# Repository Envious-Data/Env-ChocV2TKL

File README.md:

# Env-ChocV2TKL
A Compact TKL layout utilizing Choc V2s and a Raspberry Pi Pico

### What this is
This is an experiment/concept, Ive been wanting a choc keyboard for a while but finding keycaps for choc V1s is rather difficult. There are also almost no ISO Keycap sets that would go on a TKL HOWEVER! it appears Choc V2s are more alike cherry LP switches which fit normal MX keycaps, they have a different footprint to Choc V1s and MX style switches (which Cherry LP is also not like normal MX).

###
feel free to steal the Choc V2 footprint out of here but, I made it by modifying the choc V1 footprint and just adjusted/resized a couple bits to fit but im not wholly sure if its correct.. well it should be as per the dimentions listed by Kailh.

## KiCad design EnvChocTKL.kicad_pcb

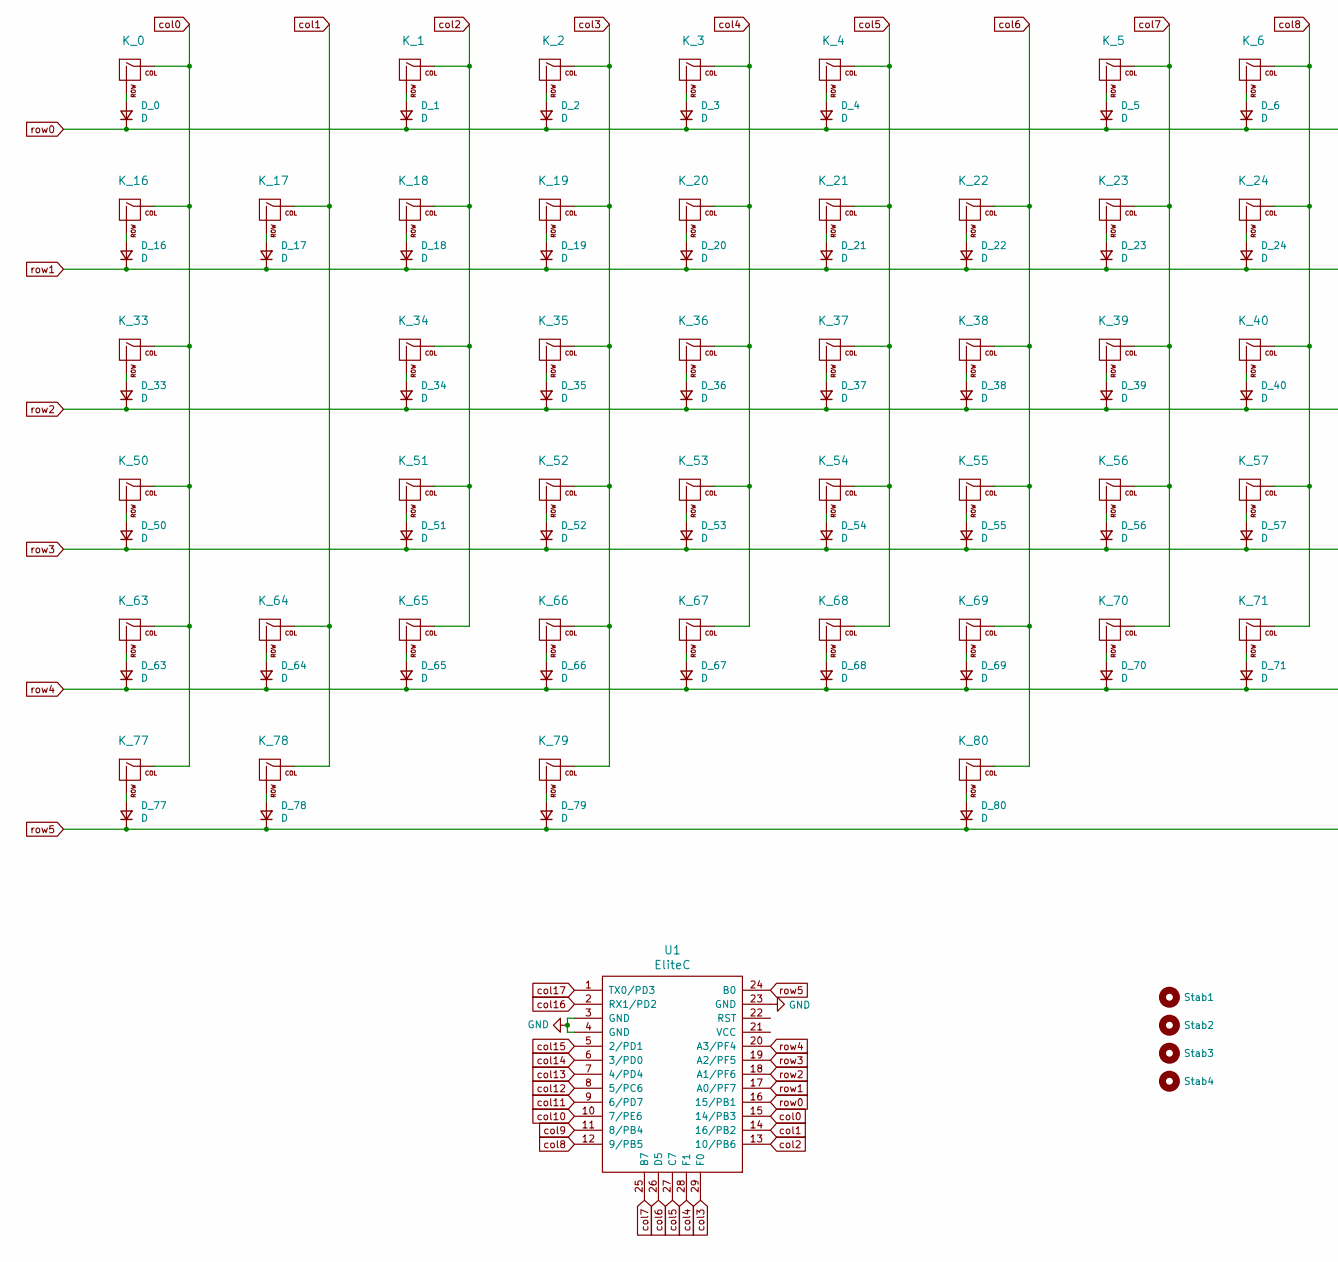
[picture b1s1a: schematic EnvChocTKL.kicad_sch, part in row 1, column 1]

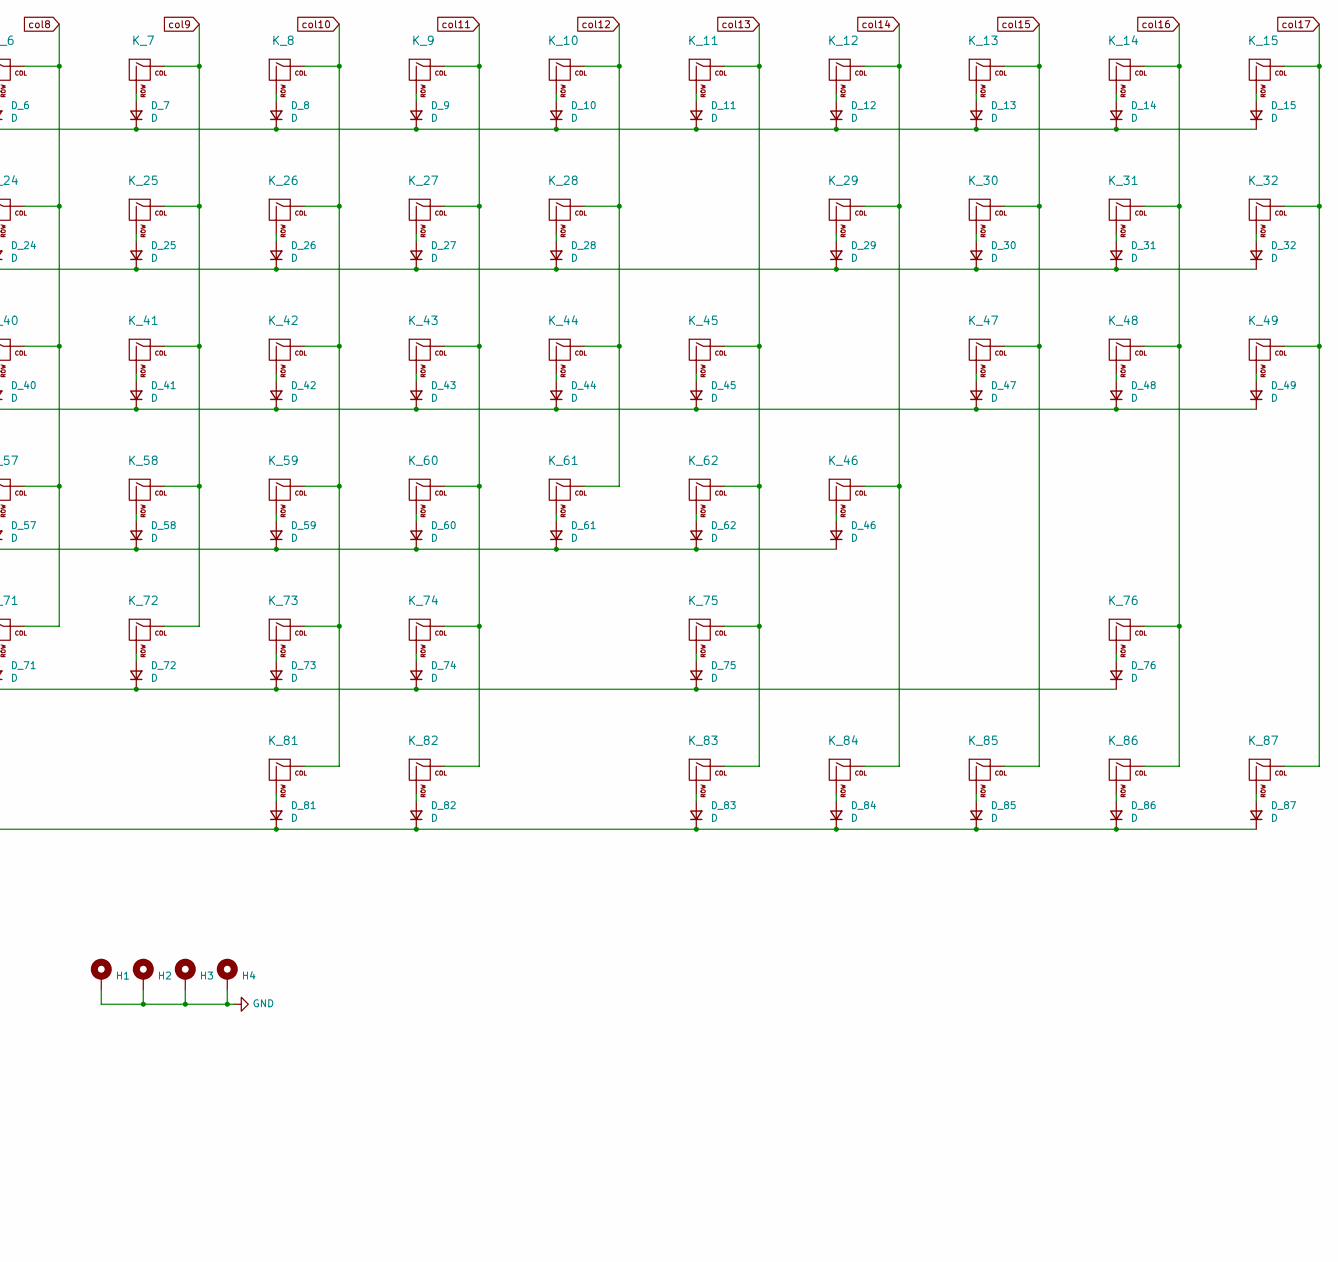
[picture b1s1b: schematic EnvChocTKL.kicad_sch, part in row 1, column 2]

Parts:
D_0, D_1, D_2, D_3, D_4, D_5, D_6, D_7, D_8, D_9, D_10, D_11, D_12, D_13, D_14, D_15, D_16, D_17, D_18, D_19, D_20, D_21, D_22, D_23, D_24, D_25, D_26, D_27, D_28, D_29, D_30, D_31, D_32, D_33, D_34, D_35, D_36, D_37, D_38, D_39, D_40, D_41, D_42, D_43, D_44, D_45, D_46, D_47, D_48, D_49, D_50, D_51, D_52, D_53, D_54, D_55, D_56, D_57, D_58, D_59, D_60, D_61, D_62, D_63, D_64, D_65, D_66, D_67, D_68, D_69, D_70, D_71, D_72, D_73, D_74, D_75, D_76, D_77, D_78, D_79, D_80, D_81, D_82, D_83, D_84, D_85, D_86, D_87: D; D_SOD-123
H1, H2, H3, H4: MountingHole_Pad; MountingHole_2.5mm_Pad
K_0, K_1, K_2, K_3, K_4, K_5, K_6, K_7, K_8, K_9, K_10, K_11, K_12, K_13, K_14, K_15, K_16, K_17, K_18, K_19, K_20, K_21, K_22, K_23, K_24, K_25, K_26, K_27, K_28, K_29, K_30, K_31, K_32, K_33, K_34, K_35, K_36, K_37, K_38, K_39, K_40, K_41, K_42, K_43, K_44, K_45, K_46, K_47, K_48, K_49, K_50, K_51, K_52, K_53, K_54, K_55, K_56, K_57, K_58, K_59, K_60, K_61, K_62, K_63, K_64, K_65, K_66, K_67, K_68, K_69, K_70, K_71, K_72, K_73, K_74, K_75, K_76, K_77, K_78, K_79, K_80, K_81, K_82, K_83, K_84, K_85, K_86, K_87: KEYSW; SW_Kailh_Choc_V2
Stab1, Stab2, Stab3: MountingHole_Pad; Stabilizer_Cherry_MX_2u
Stab4: MountingHole_Pad; Stabilizer_Cherry_MX_6.25u
U1: EliteC; Elite-C

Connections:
GND: H1.1, H2.1, H3.1, H4.1, U1.3 (GND), U1.4 (GND), U1.23 (GND)
unnamed: D_0.2 (A), K_0.2 (ROW)
unnamed: D_1.2 (A), K_1.2 (ROW)
unnamed: D_2.2 (A), K_2.2 (ROW)
unnamed: D_3.2 (A), K_3.2 (ROW)
unnamed: D_4.2 (A), K_4.2 (ROW)
unnamed: D_5.2 (A), K_5.2 (ROW)
unnamed: D_6.2 (A), K_6.2 (ROW)
unnamed: D_7.2 (A), K_7.2 (ROW)
unnamed: D_8.2 (A), K_8.2 (ROW)
unnamed: D_9.2 (A), K_9.2 (ROW)
unnamed: D_10.2 (A), K_10.2 (ROW)
unnamed: D_11.2 (A), K_11.2 (ROW)
unnamed: D_12.2 (A), K_12.2 (ROW)
unnamed: D_13.2 (A), K_13.2 (ROW)
unnamed: D_14.2 (A), K_14.2 (ROW)
unnamed: D_15.2 (A), K_15.2 (ROW)
unnamed: D_16.2 (A), K_16.2 (ROW)
unnamed: D_17.2 (A), K_17.2 (ROW)
unnamed: D_18.2 (A), K_18.2 (ROW)
unnamed: D_19.2 (A), K_19.2 (ROW)
unnamed: D_20.2 (A), K_20.2 (ROW)
unnamed: D_21.2 (A), K_21.2 (ROW)
unnamed: D_22.2 (A), K_22.2 (ROW)
unnamed: D_23.2 (A), K_23.2 (ROW)
unnamed: D_24.2 (A), K_24.2 (ROW)
unnamed: D_25.2 (A), K_25.2 (ROW)
unnamed: D_26.2 (A), K_26.2 (ROW)
unnamed: D_27.2 (A), K_27.2 (ROW)
unnamed: D_28.2 (A), K_28.2 (ROW)
unnamed: D_29.2 (A), K_29.2 (ROW)
unnamed: D_30.2 (A), K_30.2 (ROW)
unnamed: D_31.2 (A), K_31.2 (ROW)
unnamed: D_32.2 (A), K_32.2 (ROW)
unnamed: D_33.2 (A), K_33.2 (ROW)
unnamed: D_34.2 (A), K_34.2 (ROW)
unnamed: D_35.2 (A), K_35.2 (ROW)
unnamed: D_36.2 (A), K_36.2 (ROW)
unnamed: D_37.2 (A), K_37.2 (ROW)
unnamed: D_38.2 (A), K_38.2 (ROW)
unnamed: D_39.2 (A), K_39.2 (ROW)
unnamed: D_40.2 (A), K_40.2 (ROW)
unnamed: D_41.2 (A), K_41.2 (ROW)
unnamed: D_42.2 (A), K_42.2 (ROW)
unnamed: D_43.2 (A), K_43.2 (ROW)
unnamed: D_44.2 (A), K_44.2 (ROW)
unnamed: D_45.2 (A), K_45.2 (ROW)
unnamed: D_46.2 (A), K_46.2 (ROW)
unnamed: D_47.2 (A), K_47.2 (ROW)
unnamed: D_48.2 (A), K_48.2 (ROW)
unnamed: D_49.2 (A), K_49.2 (ROW)
unnamed: D_50.2 (A), K_50.2 (ROW)
unnamed: D_51.2 (A), K_51.2 (ROW)
unnamed: D_52.2 (A), K_52.2 (ROW)
unnamed: D_53.2 (A), K_53.2 (ROW)
unnamed: D_54.2 (A), K_54.2 (ROW)
unnamed: D_55.2 (A), K_55.2 (ROW)
unnamed: D_56.2 (A), K_56.2 (ROW)
unnamed: D_57.2 (A), K_57.2 (ROW)
unnamed: D_58.2 (A), K_58.2 (ROW)
unnamed: D_59.2 (A), K_59.2 (ROW)
unnamed: D_60.2 (A), K_60.2 (ROW)
unnamed: D_61.2 (A), K_61.2 (ROW)
unnamed: D_62.2 (A), K_62.2 (ROW)
unnamed: D_63.2 (A), K_63.2 (ROW)
unnamed: D_64.2 (A), K_64.2 (ROW)
unnamed: D_65.2 (A), K_65.2 (ROW)
unnamed: D_66.2 (A), K_66.2 (ROW)
unnamed: D_67.2 (A), K_67.2 (ROW)
unnamed: D_68.2 (A), K_68.2 (ROW)
unnamed: D_69.2 (A), K_69.2 (ROW)
unnamed: D_70.2 (A), K_70.2 (ROW)
unnamed: D_71.2 (A), K_71.2 (ROW)
unnamed: D_72.2 (A), K_72.2 (ROW)
unnamed: D_73.2 (A), K_73.2 (ROW)
unnamed: D_74.2 (A), K_74.2 (ROW)
unnamed: D_75.2 (A), K_75.2 (ROW)
unnamed: D_76.2 (A), K_76.2 (ROW)
unnamed: D_77.2 (A), K_77.2 (ROW)
unnamed: D_78.2 (A), K_78.2 (ROW)
unnamed: D_79.2 (A), K_79.2 (ROW)
unnamed: D_80.2 (A), K_80.2 (ROW)
unnamed: D_81.2 (A), K_81.2 (ROW)
unnamed: D_82.2 (A), K_82.2 (ROW)
unnamed: D_83.2 (A), K_83.2 (ROW)
unnamed: D_84.2 (A), K_84.2 (ROW)
unnamed: D_85.2 (A), K_85.2 (ROW)
unnamed: D_86.2 (A), K_86.2 (ROW)
unnamed: D_87.2 (A), K_87.2 (ROW)
col0: K_0.1 (COL), K_16.1 (COL), K_33.1 (COL), K_50.1 (COL), K_63.1 (COL), K_77.1 (COL), U1.15 (14/PB3)
col1: K_17.1 (COL), K_64.1 (COL), K_78.1 (COL), U1.14 (16/PB2)
col2: K_1.1 (COL), K_18.1 (COL), K_34.1 (COL), K_51.1 (COL), K_65.1 (COL), U1.13 (10/PB6)
col3: K_2.1 (COL), K_19.1 (COL), K_35.1 (COL), K_52.1 (COL), K_66.1 (COL), K_79.1 (COL), U1.29 (F0)
col4: K_3.1 (COL), K_20.1 (COL), K_36.1 (COL), K_53.1 (COL), K_67.1 (COL), U1.28 (F1)
col5: K_4.1 (COL), K_21.1 (COL), K_37.1 (COL), K_54.1 (COL), K_68.1 (COL), U1.27 (C7)
col6: K_22.1 (COL), K_38.1 (COL), K_55.1 (COL), K_69.1 (COL), K_80.1 (COL), U1.26 (D5)
col7: K_5.1 (COL), K_23.1 (COL), K_39.1 (COL), K_56.1 (COL), K_70.1 (COL), U1.25 (B7)
col8: K_6.1 (COL), K_24.1 (COL), K_40.1 (COL), K_57.1 (COL), K_71.1 (COL), U1.12 (9/PB5)
col9: K_7.1 (COL), K_25.1 (COL), K_41.1 (COL), K_58.1 (COL), K_72.1 (COL), U1.11 (8/PB4)
col10: K_8.1 (COL), K_26.1 (COL), K_42.1 (COL), K_59.1 (COL), K_73.1 (COL), K_81.1 (COL), U1.10 (7/PE6)
col11: K_9.1 (COL), K_27.1 (COL), K_43.1 (COL), K_60.1 (COL), K_74.1 (COL), K_82.1 (COL), U1.9 (6/PD7)
col12: K_10.1 (COL), K_28.1 (COL), K_44.1 (COL), K_61.1 (COL), U1.8 (5/PC6)
col13: K_11.1 (COL), K_45.1 (COL), K_62.1 (COL), K_75.1 (COL), K_83.1 (COL), U1.7 (4/PD4)
col14: K_12.1 (COL), K_29.1 (COL), K_46.1 (COL), K_84.1 (COL), U1.6 (3/PD0)
col15: K_13.1 (COL), K_30.1 (COL), K_47.1 (COL), K_85.1 (COL), U1.5 (2/PD1)
col16: K_14.1 (COL), K_31.1 (COL), K_48.1 (COL), K_76.1 (COL), K_86.1 (COL), U1.2 (RX1/PD2)
col17: K_15.1 (COL), K_32.1 (COL), K_49.1 (COL), K_87.1 (COL), U1.1 (TX0/PD3)
row0: D_0.1 (K), D_1.1 (K), D_2.1 (K), D_3.1 (K), D_4.1 (K), D_5.1 (K), D_6.1 (K), D_7.1 (K), D_8.1 (K), D_9.1 (K), D_10.1 (K), D_11.1 (K), D_12.1 (K), D_13.1 (K), D_14.1 (K), D_15.1 (K), U1.16 (15/PB1)
row1: D_16.1 (K), D_17.1 (K), D_18.1 (K), D_19.1 (K), D_20.1 (K), D_21.1 (K), D_22.1 (K), D_23.1 (K), D_24.1 (K), D_25.1 (K), D_26.1 (K), D_27.1 (K), D_28.1 (K), D_29.1 (K), D_30.1 (K), D_31.1 (K), D_32.1 (K), U1.17 (A0/PF7)
row2: D_33.1 (K), D_34.1 (K), D_35.1 (K), D_36.1 (K), D_37.1 (K), D_38.1 (K), D_39.1 (K), D_40.1 (K), D_41.1 (K), D_42.1 (K), D_43.1 (K), D_44.1 (K), D_45.1 (K), D_47.1 (K), D_48.1 (K), D_49.1 (K), U1.18 (A1/PF6)
row3: D_46.1 (K), D_50.1 (K), D_51.1 (K), D_52.1 (K), D_53.1 (K), D_54.1 (K), D_55.1 (K), D_56.1 (K), D_57.1 (K), D_58.1 (K), D_59.1 (K), D_60.1 (K), D_61.1 (K), D_62.1 (K), U1.19 (A2/PF5)
row4: D_63.1 (K), D_64.1 (K), D_65.1 (K), D_66.1 (K), D_67.1 (K), D_68.1 (K), D_69.1 (K), D_70.1 (K), D_71.1 (K), D_72.1 (K), D_73.1 (K), D_74.1 (K), D_75.1 (K), D_76.1 (K), U1.20 (A3/PF4)
row5: D_77.1 (K), D_78.1 (K), D_79.1 (K), D_80.1 (K), D_81.1 (K), D_82.1 (K), D_83.1 (K), D_84.1 (K), D_85.1 (K), D_86.1 (K), D_87.1 (K), U1.24 (B0)

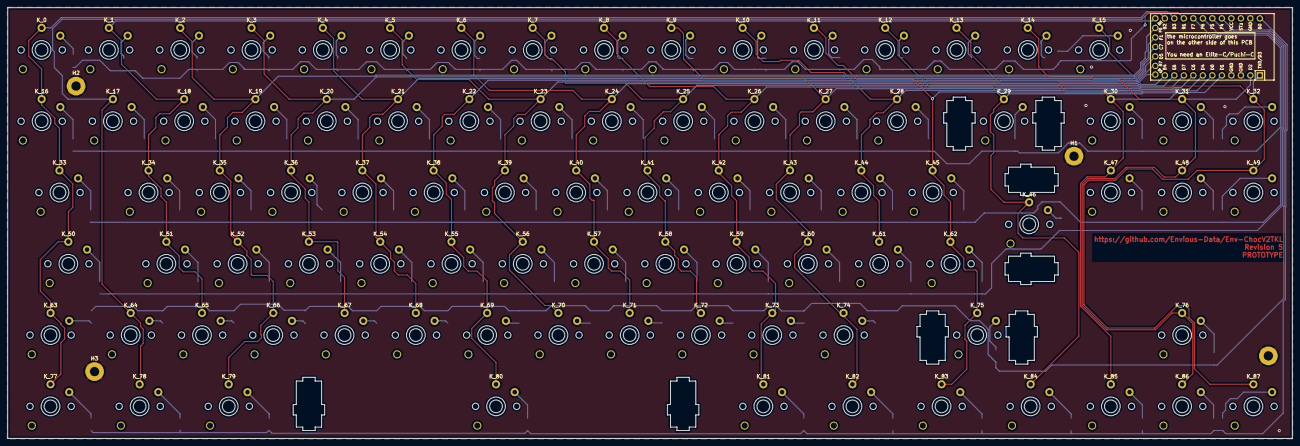
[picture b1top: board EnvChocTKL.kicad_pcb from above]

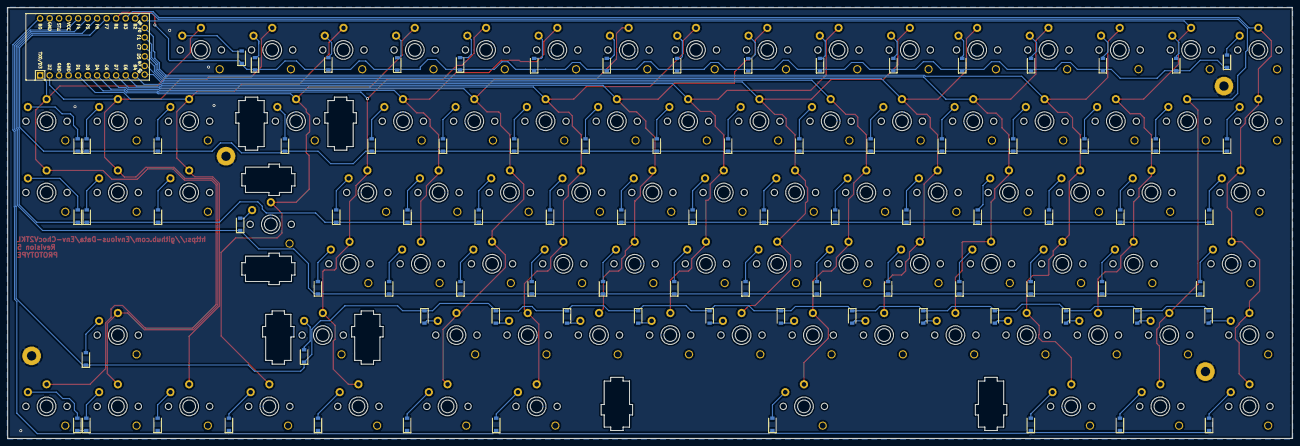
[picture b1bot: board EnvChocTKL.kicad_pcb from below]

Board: 2 copper layers, 343.3 x 115.1 mm, 181 parts (89 on the bottom side), 113 nets.

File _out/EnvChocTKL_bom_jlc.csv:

"Comment","Designator","Footprint","LCSC Part #"
"D","D_0,D_1,D_2,D_3,D_4,D_5,D_6,D_7,D_8,D_9,D_10,D_11,D_12,D_13,D_14,D_15,D_16,D_17,D_18,D_19,D_20,D_21,D_22,D_23,D_24,D_25,D_26,D_27,D_28,D_29,D_30,D_31,D_32,D_33,D_34,D_35,D_36,D_37,D_38,D_39,D_40,D_41,D_42,D_43,D_44,D_45,D_47,D_48,D_49,D_50,D_51,D_52,D_53,D_54,D_55,D_56,D_57,D_58,D_59,D_60,D_61,D_62,D_46,D_63,D_64,D_65,D_66,D_67,D_68,D_69,D_70,D_71,D_72,D_73,D_74,D_75,D_76,D_77,D_78,D_79,D_80,D_81,D_82,D_83,D_84,D_85,D_86,D_87","D_SOD-123","no_part_number"
"MountingHole_Pad","H1,H2,H3,H4","MountingHole_2.5mm_Pad","no_part_number"
"KEYSW","K_0,K_1,K_2,K_3,K_4,K_5,K_6,K_7,K_8,K_9,K_10,K_11,K_12,K_13,K_14,K_15,K_16,K_17,K_18,K_19,K_20,K_21,K_22,K_23,K_24,K_25,K_26,K_27,K_28,K_29,K_30,K_31,K_32,K_33,K_34,K_35,K_36,K_37,K_38,K_39,K_40,K_41,K_42,K_43,K_44,K_45,K_47,K_48,K_49,K_50,K_51,K_52,K_53,K_54,K_55,K_56,K_57,K_58,K_59,K_60,K_61,K_62,K_46,K_63,K_64,K_65,K_66,K_67,K_68,K_69,K_70,K_71,K_72,K_73,K_74,K_75,K_76,K_77,K_78,K_79,K_80,K_81,K_82,K_83,K_84,K_85,K_86,K_87","SW_Kailh_Choc_V2","no_part_number"
"MountingHole_Pad","Stab1,Stab2,Stab3","Stabilizer_Cherry_MX_2u","no_part_number"
"MountingHole_Pad","Stab4","Stabilizer_Cherry_MX_6.25u","no_part_number"
"EliteC","U1","Elite-C","no_part_number"

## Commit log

2021-09-11 added mount holes, a few silkscreen marks and generated revision 0 gerber
2021-09-11 forgot to save changes to pcbnew
2021-09-11 Corrected some errors and generated a fixed gerber
2021-09-11 small name correction
2021-09-19 updated Choc V2 footprint
2021-11-19 swapped footprint to sort of fit chocV1 as well and corrected all DRC errors
2021-11-22 replaced stabs with cutouts for lower profile mounting and fixed issues relating to such, generated updated gerber
2021-11-22 changed cutout shape and generated another gerber
2021-11-22 moved MCU and redid a bunch of traces
2021-11-22 added mount holes and adjusted some traces in relation
2021-11-22 updated silkscreen and ran cleanup
2021-11-25 adjusted cutouts and related, also orderd this version via jlc.
2021-11-26 DERP! - missing trace, D12 to pin2 of Switch 12
2021-12-09 fixed issues with footprint and required board changes + updated gerber
2021-12-09 adjusted couple traces and sorted out revision
2021-12-26 refined design a bit by spacing function row and nav cluster apart just a bit, moved some other parts and started work on stabilizer footprints
2021-12-27 fixed some issues as per DRC
2022-01-11 some changes I forgot to commit.
2022-02-23 converted MCU from elite-c to onboard RP2040
2022-02-23 ground unconnected for some deoupling capacitors
2022-02-23 updated gitignore
2022-02-24 updated revision
2022-02-24 fixed doubled hole on footprint and adjusted board settings to comply with JLCPCB Capabilities.
2022-03-07 flipped MCU to other side
    might optimize the space usage of the MCU so I can have a more normal top row.
2022-03-07 generated updated Gerbers and made appropriate part changes
2022-03-09 swapped flash for lager SOIC-8 and removed some parts.
2022-03-12 IMPORTANT FIX
    for some reason a lot of the switches were slightly misaligned to MX spacing and also added cutouts for Choc stabs on Eco.User to be exported as DXF for whatever.
2022-04-01 Swapped MCU from onboard RP2040 to RPI PICO
2022-04-03 modified PCB design to be cheaper, 0.15mm thick tracks, 0.2mm spacing, 0.8/0.4mm vias.
2022-04-04 updated Readme and file organization
2022-04-09 added mid-mount type-c port, swapped onboard MCU for pico and also couple more mount holes, various other adjustments i.e backplate n stuff
2022-04-09 added mount hole cutouts to user eco layers.
2022-05-18 made usb pin cutout larger for ease of soldering.
2022-06-07 generated updated gerber
2022-06-18 modified footprint to have TP6 and added reset and bootsel buttons
2022-12-08 generated gerber and 3d model
2022-12-16 made backplate and switch plate as well as adjusted main pcb mount holes for standoffs
2022-12-16 smol fix
2023-01-09 moved gerbers to their own folder + removed old versions since git will record that.
2024-07-27 checks and preparation to order
2024-08-05 Generated production files
